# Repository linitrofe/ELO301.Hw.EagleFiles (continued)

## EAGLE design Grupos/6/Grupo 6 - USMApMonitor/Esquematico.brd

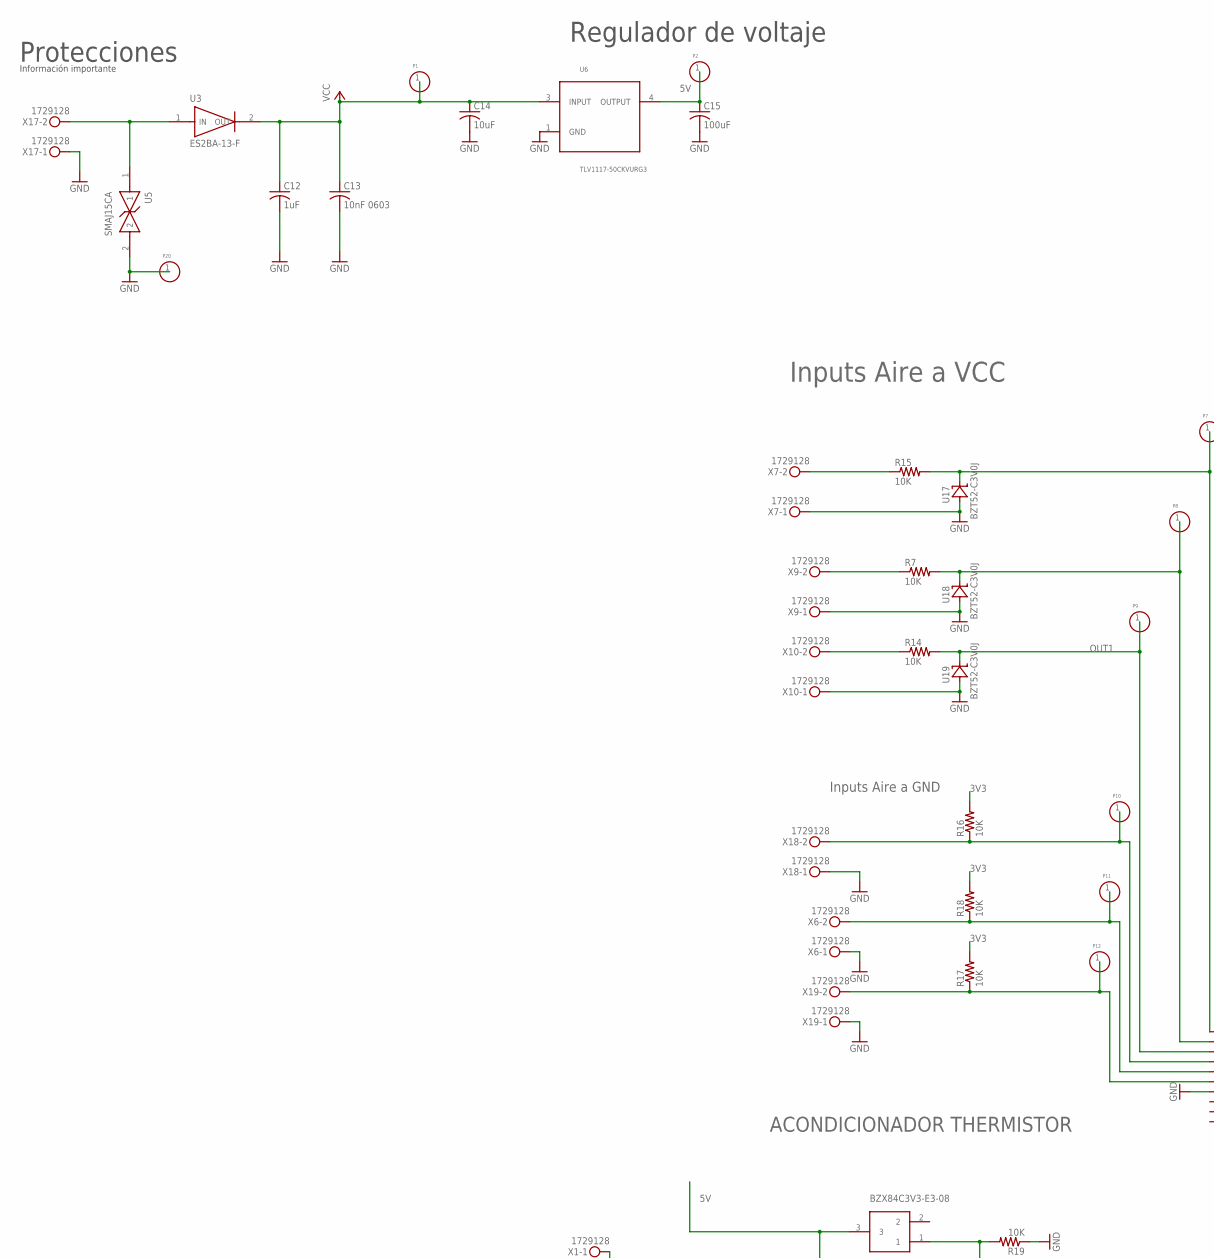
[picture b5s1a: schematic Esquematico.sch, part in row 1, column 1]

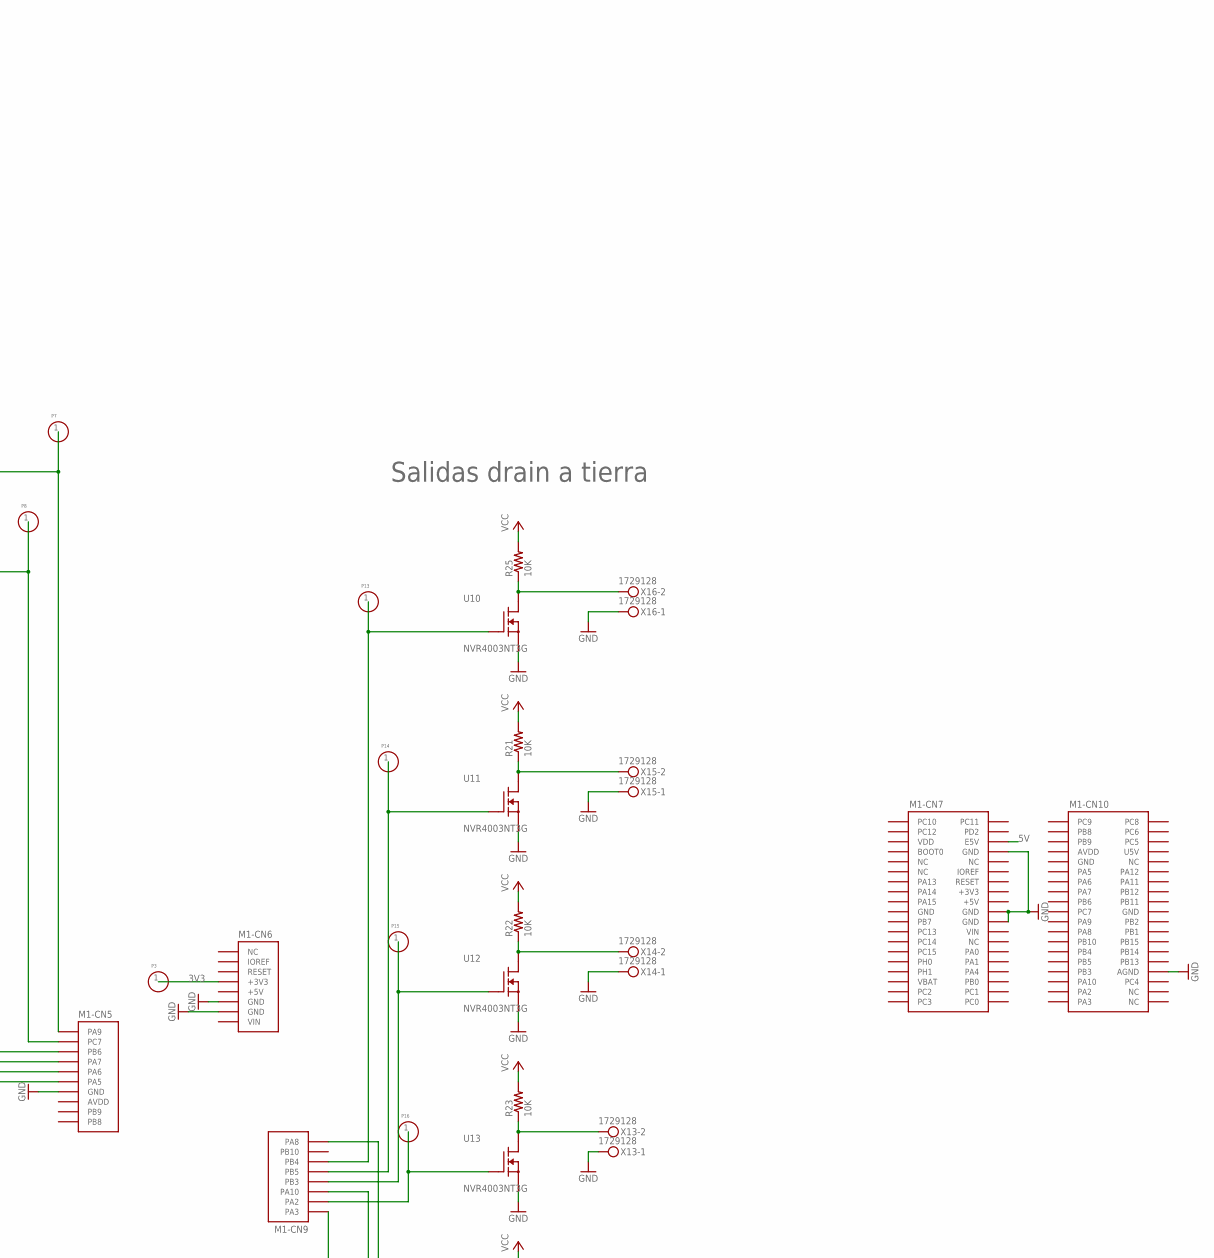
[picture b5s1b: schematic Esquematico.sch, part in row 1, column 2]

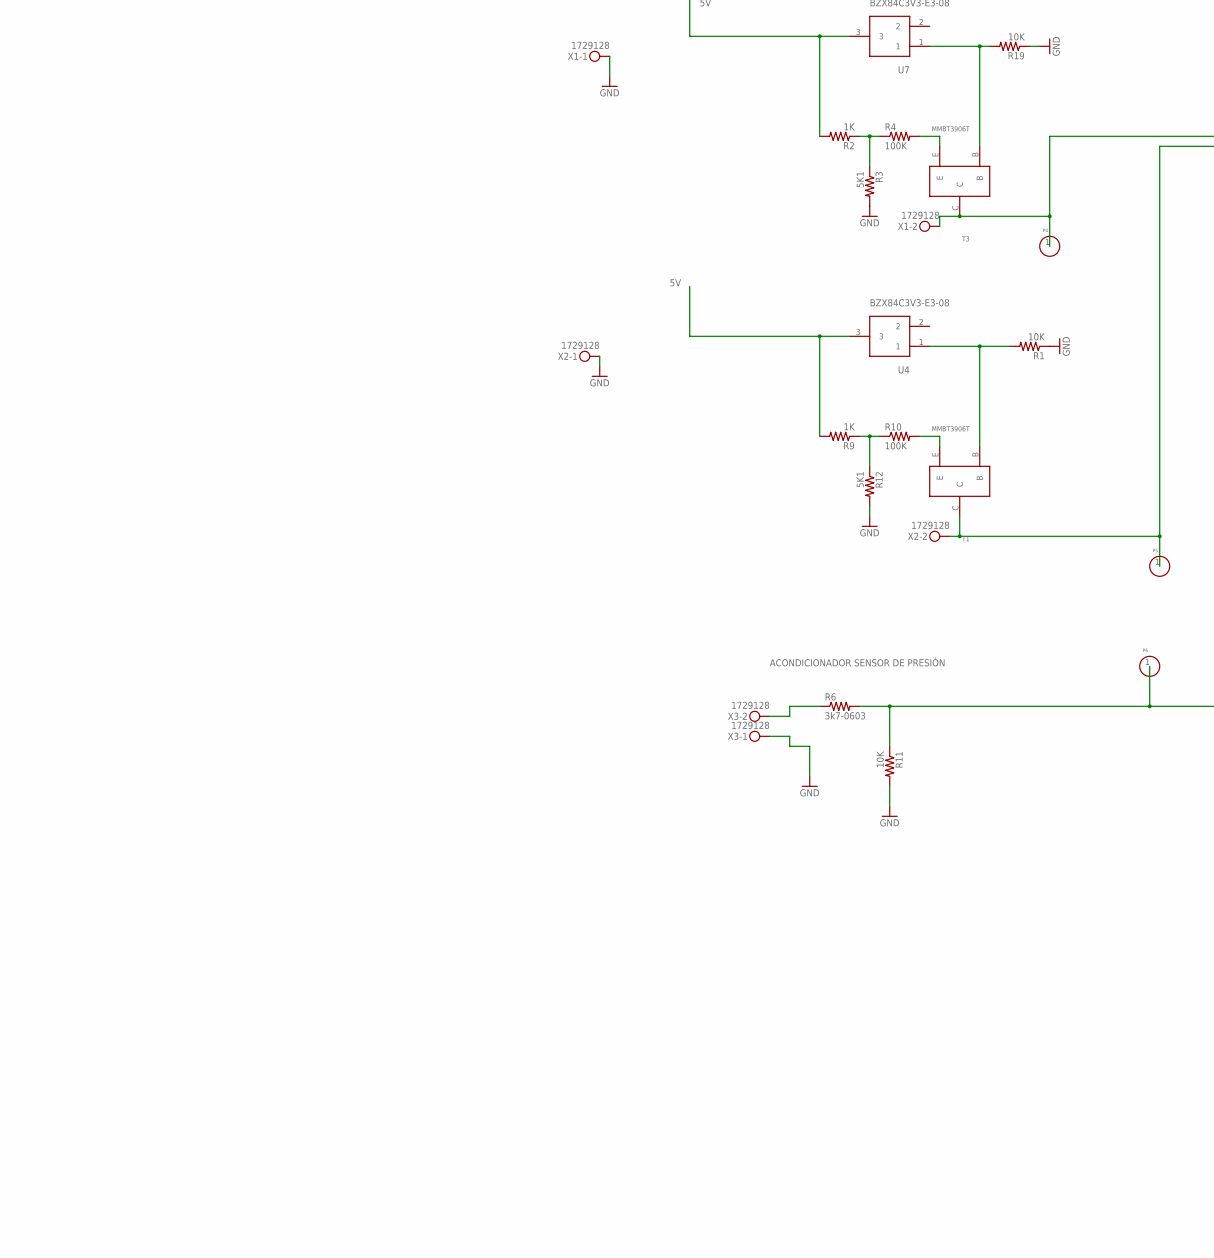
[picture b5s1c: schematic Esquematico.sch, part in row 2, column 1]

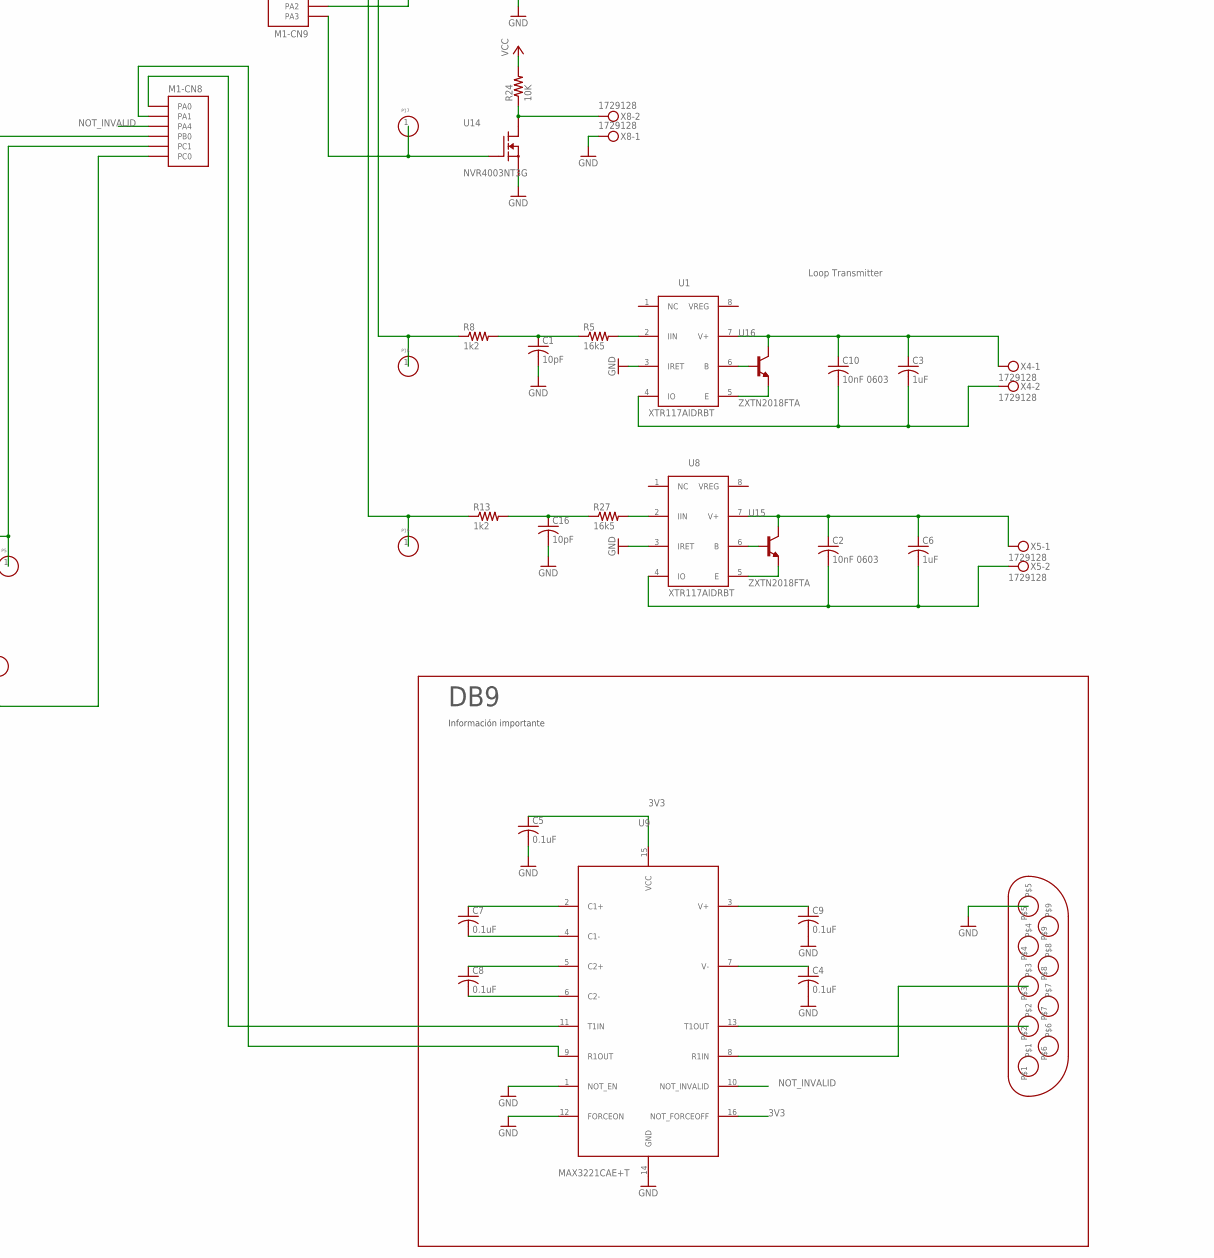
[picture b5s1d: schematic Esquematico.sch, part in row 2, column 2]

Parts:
C1, C16: 10pF; C0805; PARTNO 0805D100J101KHT
C2, C10, C13: 10nF 0603; C0603; PARTNO GCM188R72A103KA37D
C3, C6, C12: 1uF; C0805; PARTNO GCM21BR71E105KA56L
C4, C5, C7, C8, C9: 0.1uF; C0805; PARTNO GCM21BR72A104KA37L
C14: 10uF; C0805; PARTNO TCTPL1C106M8R
C15: 100uF; C0805; PARTNO TLJP107M006R5400
M1: NUCLEO-L452RE; NUCLEO-64; PARTNO NUCLEO-L452RE
P1, P2, P3, P4, P5, P6, P7, P8, P9, P10, P11, P12, P13, P14, P15, P16, P17, P18, P19, P20: TESTPOINT
R1, R7, R11, R14, R15, R16, R17, R18, R19, R21, R22, R23, R24, R25: 10K; R0805; PARTNO RK73G2ATTD1002F
R2, R9: 1K; R0805; PARTNO AC0805FR-101KL
R3, R12: 5K1; R0805; PARTNO ESR10EZPJ512
R4, R10: 100K; R0805; PARTNO AT0805FRE07100KL
R5, R27: 16k5; R0805; PARTNO ERJ-PB6B1652V
R6: 3k7-0603; R0603; PARTNO RN73H1JTTD3701B25
R8, R13: 1k2; R0805; PARTNO ESR10EZPF1R20
T1, T3: MMBT3906T; SOT-523; PARTNO MMBT3906T
U1, U8: XTR117AIDRBT; 8-SON; PARTNO XTR117AIDRBT
U2: D09P33E4GX00LF; JEDEC; PARTNO D09P33E4GX00LF
U3: ES2BA-13-F; SMA; PARTNO ES2BA-13-F
U4, U7: BZX84C3V3-E3-08; SOT-23-3; PARTNO BZX84C3V3-E3-08
U5: SMAJ15CA; DO-214AC(SMA); PARTNO SMAJ15CA
U6: TLV1117-50CKVURG3; KVU(TO-252); PARTNO TLV1117-50CKVURG3
U9: MAX3221CAE+T; 16-SSOP; PARTNO MAX3221CAE+T
U10, U11, U12, U13, U14: NVR4003NT3G; SOT-23-3; PARTNO NVR4003NT3G
U15, U16: ZXTN2018FTA; SOT23-EBC; PARTNO ZXTN2018FTA
U17, U18, U19: BZT52-C3V0J; BZT52-C3V0J-NEXPERIA; PARTNO BZT52-C3V0J
X1, X2, X3, X4, X5, X6, X7, X8, X9, X10, X13, X14, X15, X16, X17, X18, X19: 1729128; MKDSN1,5/2-5,08; PARTNO 1729128

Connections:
3V3: C5.1, M1.CN6-4 (+3V3), P3.1, R16.2, R17.2, R18.2, U9.15 (VCC), U9.16 (NOT_FORCEOFF)
5V: C15.1, M1.CN7-6 (E5V), P2.1, R2.2, R9.2, U4.3, U6.4 (OUTPUT), U7.3
+3V3: M1.CN7-16 (+3V3)
+5V: M1.CN6-5 (+5V), M1.CN7-18 (+5V)
AVDD: M1.CN5-8 (AVDD), M1.CN10-7 (AVDD)
GND: C1.2, C4.2, C5.2, C9.2, C12.2, C13.2, C14.2, C15.2, C16.2, M1.CN5-7 (GND), M1.CN6-6 (GND), M1.CN6-7 (GND), M1.CN7-8 (GND), M1.CN7-19 (GND), M1.CN7-20 (GND), M1.CN7-22 (GND), M1.CN10-9 (GND), M1.CN10-20 (GND), M1.CN10-32 (AGND), P20.1, R1.1, R3.2, R11.2, R12.2, R19.1, U1.3 (IRET), U2.P$5, U5.2, U6.1 (GND), U8.3 (IRET), U9.1 (NOT_EN), U9.12 (FORCEON), U9.14 (GND), U10.2 (SOURCE), U11.2 (SOURCE), U12.2 (SOURCE), U13.2 (SOURCE), U14.2 (SOURCE), U17.1 (ANODE), U18.1 (ANODE), U19.1 (ANODE), X1.1, X2.1, X3.1, X6.1, X7.1, X8.1, X9.1, X10.1, X13.1, X14.1, X15.1, X16.1, X17.1, X18.1, X19.1
IOREF: M1.CN6-2 (IOREF)
unnamed: R19.2, T3.B, U7.1
unnamed: R2.1, R3.1, R4.1
unnamed: R4.2, T3.E
unnamed: M1.CN9-8 (PA8), P18.1, R8.1
unnamed: M1.CN8-6 (PC0), P6.1, R6.2, R11.1
unnamed: R6.1, X3.2
unnamed: C1.1, R5.1, R8.2
unnamed: R5.2, U1.2 (IIN)
unnamed: C16.1, R13.2, R27.1
unnamed: C3.2, C10.2, U1.4 (IO), X4.2
unnamed: U1.6 (B), U16.B
unnamed: U1.5 (E), U16.E
unnamed: R1.2, T1.B, U4.1
unnamed: R9.1, R10.1, R12.1
unnamed: R10.2, T1.E
unnamed: M1.CN8-5 (PC1), P5.1, T1.C, X2.2
unnamed: C3.1, C10.1, U1.7 (V+), U16.C, X4.1
unnamed: R27.2, U8.2 (IIN)
unnamed: C2.2, C6.2, U8.4 (IO), X5.2
unnamed: U8.6 (B), U15.B
unnamed: U8.5 (E), U15.E
unnamed: C2.1, C6.1, U8.7 (V+), U15.C, X5.1
unnamed: R15.1, X7.2
unnamed: M1.CN5-1 (PA9), P7.1, R15.2, U17.2 (CATODE)
unnamed: M1.CN5-4 (PA7), P10.1, R16.1, X18.2
unnamed: R7.1, X9.2
unnamed: M1.CN5-2 (PC7), P8.1, R7.2, U18.2 (CATODE)
unnamed: R14.1, X10.2
unnamed: M1.CN5-5 (PA6), P11.1, R18.1, X6.2
unnamed: M1.CN5-6 (PA5), P12.1, R17.1, X19.2
unnamed: R21.1, U11.3 (DRAIN), X15.2
unnamed: M1.CN9-5 (PB5), P14.1, U11.1 (GATE)
unnamed: R22.1, U12.3 (DRAIN), X14.2
unnamed: M1.CN9-4 (PB3), P15.1, U12.1 (GATE)
unnamed: R23.1, U13.3 (DRAIN), X13.2
unnamed: M1.CN9-2 (PA2), P16.1, U13.1 (GATE)
unnamed: R24.1, U14.3 (DRAIN), X8.2
unnamed: M1.CN9-1 (PA3), P17.1, U14.1 (GATE)
unnamed: R25.1, U10.3 (DRAIN), X16.2
unnamed: M1.CN9-6 (PB4), P13.1, U10.1 (GATE)
unnamed: M1.CN9-3 (PA10), P19.1, R13.1
unnamed: M1.CN8-4 (PB0), P4.1, T3.C, X1.2
unnamed: C4.1, U9.7 (V-)
unnamed: C9.1, U9.3 (V+)
unnamed: C7.1, U9.2 (C1+)
unnamed: C7.2, U9.4 (C1-)
unnamed: C8.1, U9.5 (C2+)
unnamed: C8.2, U9.6 (C2-)
unnamed: U2.P$2, U9.13 (T1OUT)
unnamed: U2.P$3, U9.8 (R1IN)
unnamed: U3.1 (IN), U5.1, X17.2
unnamed: M1.CN8-1 (PA0), U9.11 (T1IN)
unnamed: M1.CN8-2 (PA1), U9.9 (R1OUT)
NOT_INVALID: M1.CN8-3 (PA4), U9.10 (NOT_INVALID)
OUT1: M1.CN5-3 (PB6), P9.1, R14.2, U19.2 (CATODE)
U5V: M1.CN10-8 (U5V)
VBAT: M1.CN7-33 (VBAT)
VCC: C12.1, C13.1, C14.1, P1.1, R21.2, R22.2, R23.2, R24.2, R25.2, U3.2 (OUT), U6.3 (INPUT)
VDD: M1.CN7-5 (VDD)
VIN: M1.CN6-8 (VIN), M1.CN7-24 (VIN)

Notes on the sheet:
ACONDICIONADOR THERMISTOR
ACONDICIONADOR SENSOR DE PRESIÓN
Salidas drain a tierra
Inputs Aire a VCC
Inputs Aire a GND
Loop Transmitter
DB9
Información importante
Protecciones
Regulador de voltaje

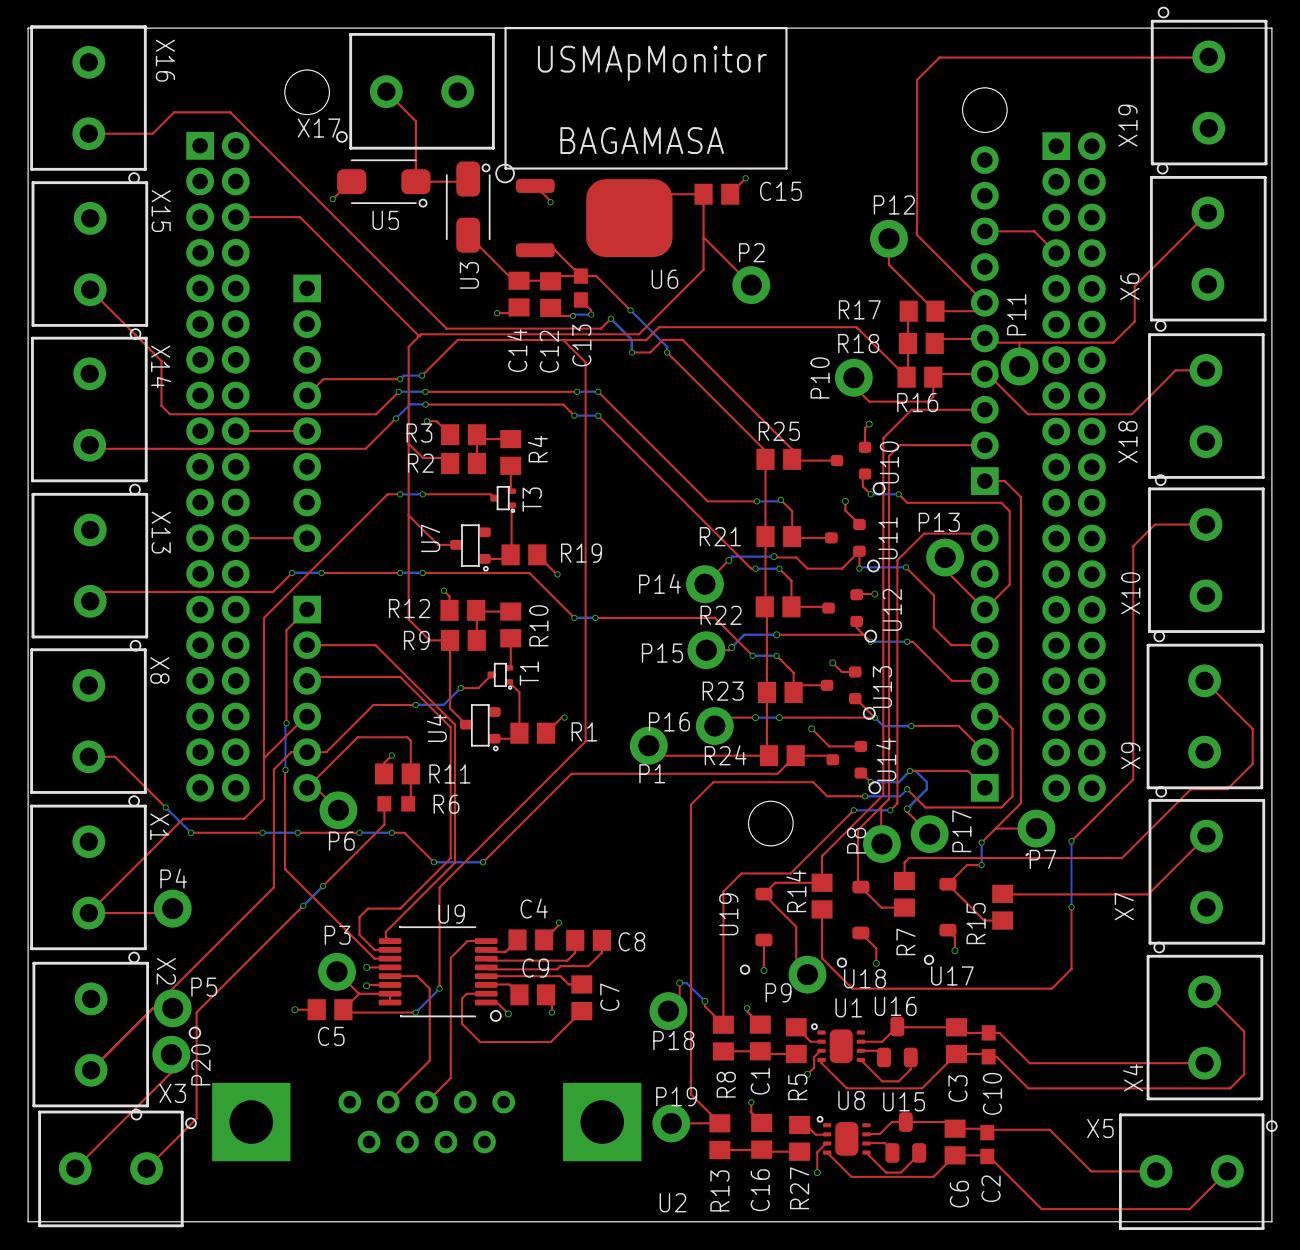
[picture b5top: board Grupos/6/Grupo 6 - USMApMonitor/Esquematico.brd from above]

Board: 2 copper layers, 88.6 x 85.0 mm, 99 parts (0 on the bottom side), 62 nets.

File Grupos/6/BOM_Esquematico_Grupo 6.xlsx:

Qty | Value | Device | Package | Parts | Description | PARTNO | POPULARITY | SPICEPREFIX | Column1
3 | BZT52-C3V0J | BZT52-C3V0J-NEXPERIA | BZT52-C3V0J-NEXPERIA | U17, U18, U19 |  | BZT52-C3V0J
2 | BZX84C3V3-E3-08 | BZX84C3V3-E3-08_VISHAY | SOT-23-3 | U4, U7 |  | BZX84C3V3-E3-08
3 | 10nF 0603 | C-USC0603 | C0603 | C2, C10, C13 | CAPACITOR, American symbol | GCM188R72A103KA37D | 37 | C
2 | 10pF | C-USC0805 | C0805 | C1, C16 | CAPACITOR, American symbol | 0805D100J101KHT | 63 | C
3 | 1uF | C-USC0805 | C0805 | C3, C6, C12 | CAPACITOR, American symbol | GCM21BR71E105KA56L | 63 | C
5 | 0.1uF | C-USC0805 | C0805 | C4, C5, C7, C8, C9 | CAPACITOR, American symbol | GCM21BR72A104KA37L | 63 | C
1 | 10uF | C-USC0805 | C0805 | C14 | CAPACITOR, American symbol | TCTPL1C106M8R | 63 | C
1 | 100uF | C-USC0805 | C0805 | C15 | CAPACITOR, American symbol | TLJP107M006R5400 | 63 | C
1 | D09P33E4GX00LF | D09P33E4GX00LF | JEDEC | U2 |  | D09P33E4GX00LF
1 | ES2BA-13-F | ES2BA-13-F | SMA | U3 |  | ES2BA-13-F
1 | MAX3221CAE+T | MAX3221CAE+T-AD | 16-SSOP | U9 |  | MAX3221CAE+T
17 | 1729128 | MKDSN1,5/2-5,08 | MKDSN1,5/2-5,08 | X1, X2, X3, X4, X5, X6, X7, X8, X9, X10, X13, X14, X15, X16, X17, X18, X19 | MKDSN 1,5/ 2-5,08 Printklemme | 1729128 | 14
2 | MMBT3906T | MMBT3906T | SOT-523 | T1, T3 |  | MMBT3906T
1 | NUCLEO-L452RE | NUCLEO-L452RE | NUCLEO-64 | M1 | No existe un outline (Layer Dimension) para esta librería. En su lugar se utili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 | NUCLEO-L452RE
5 | NVR4003NT3G | NVR4003NT3-ONSEMI | SOT-23-3 | U10, U11, U12, U13, U14 |  | NVR4003NT3G
1 | 3k7-0603 | R-US_R0603 | R0603 | R6 | RESISTOR, American symbol | RN73H1JTTD3701B25 | 77 | R
2 | 1K | R-US_R0805 | R0805 | R2, R9 | RESISTOR, American symbol | AC0805FR-101KL | 85 | R
2 | 100K | R-US_R0805 | R0805 | R4, R10 | RESISTOR, American symbol | AT0805FRE07100KL | 85 | R
2 | 16k5 | R-US_R0805 | R0805 | R5, R27 | RESISTOR, American symbol | ERJ-PB6B1652V | 85 | R
2 | 1k2 | R-US_R0805 | R0805 | R8, R13 | RESISTOR, American symbol | ESR10EZPF1R20 | 85 | R
2 | 5K1 | R-US_R0805 | R0805 | R3, R12 | RESISTOR, American symbol | ESR10EZPJ512 | 85 | R
14 | 10K | R-US_R0805 | R0805 | R1, R7, R11, R14, R15, R16, R17, R18, R19, R21, R22, R23, R24, R25 | RESISTOR, American symbol | RK73G2ATTD1002F | 85 | R
1 | SMAJ15CA | SMAJ15CA | DO-214AC(SMA) | U5 |  | SMAJ15CA
20 |  | TESTPOINT | TESTPOINT | P1, P2, P3, P4, P5, P6, P7, P8, P9, P10, P11, P12, P13, P14, P15, P16, P17, P18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
1 | TLV1117-50CKVURG3 | TLV1117-50CKVURG3 | KVU(TO-252) | U6 |  | TLV1117-50CKVURG3
2 | XTR117AIDRBT | XTR117AIDRBT-TI | 8-SON | U1, U8 |  | XTR117AIDRBT
2 | ZXTN2018FTA | ZXTN2018FTA | SOT23-EBC | U15, U16 |  | ZXTN2018FTA

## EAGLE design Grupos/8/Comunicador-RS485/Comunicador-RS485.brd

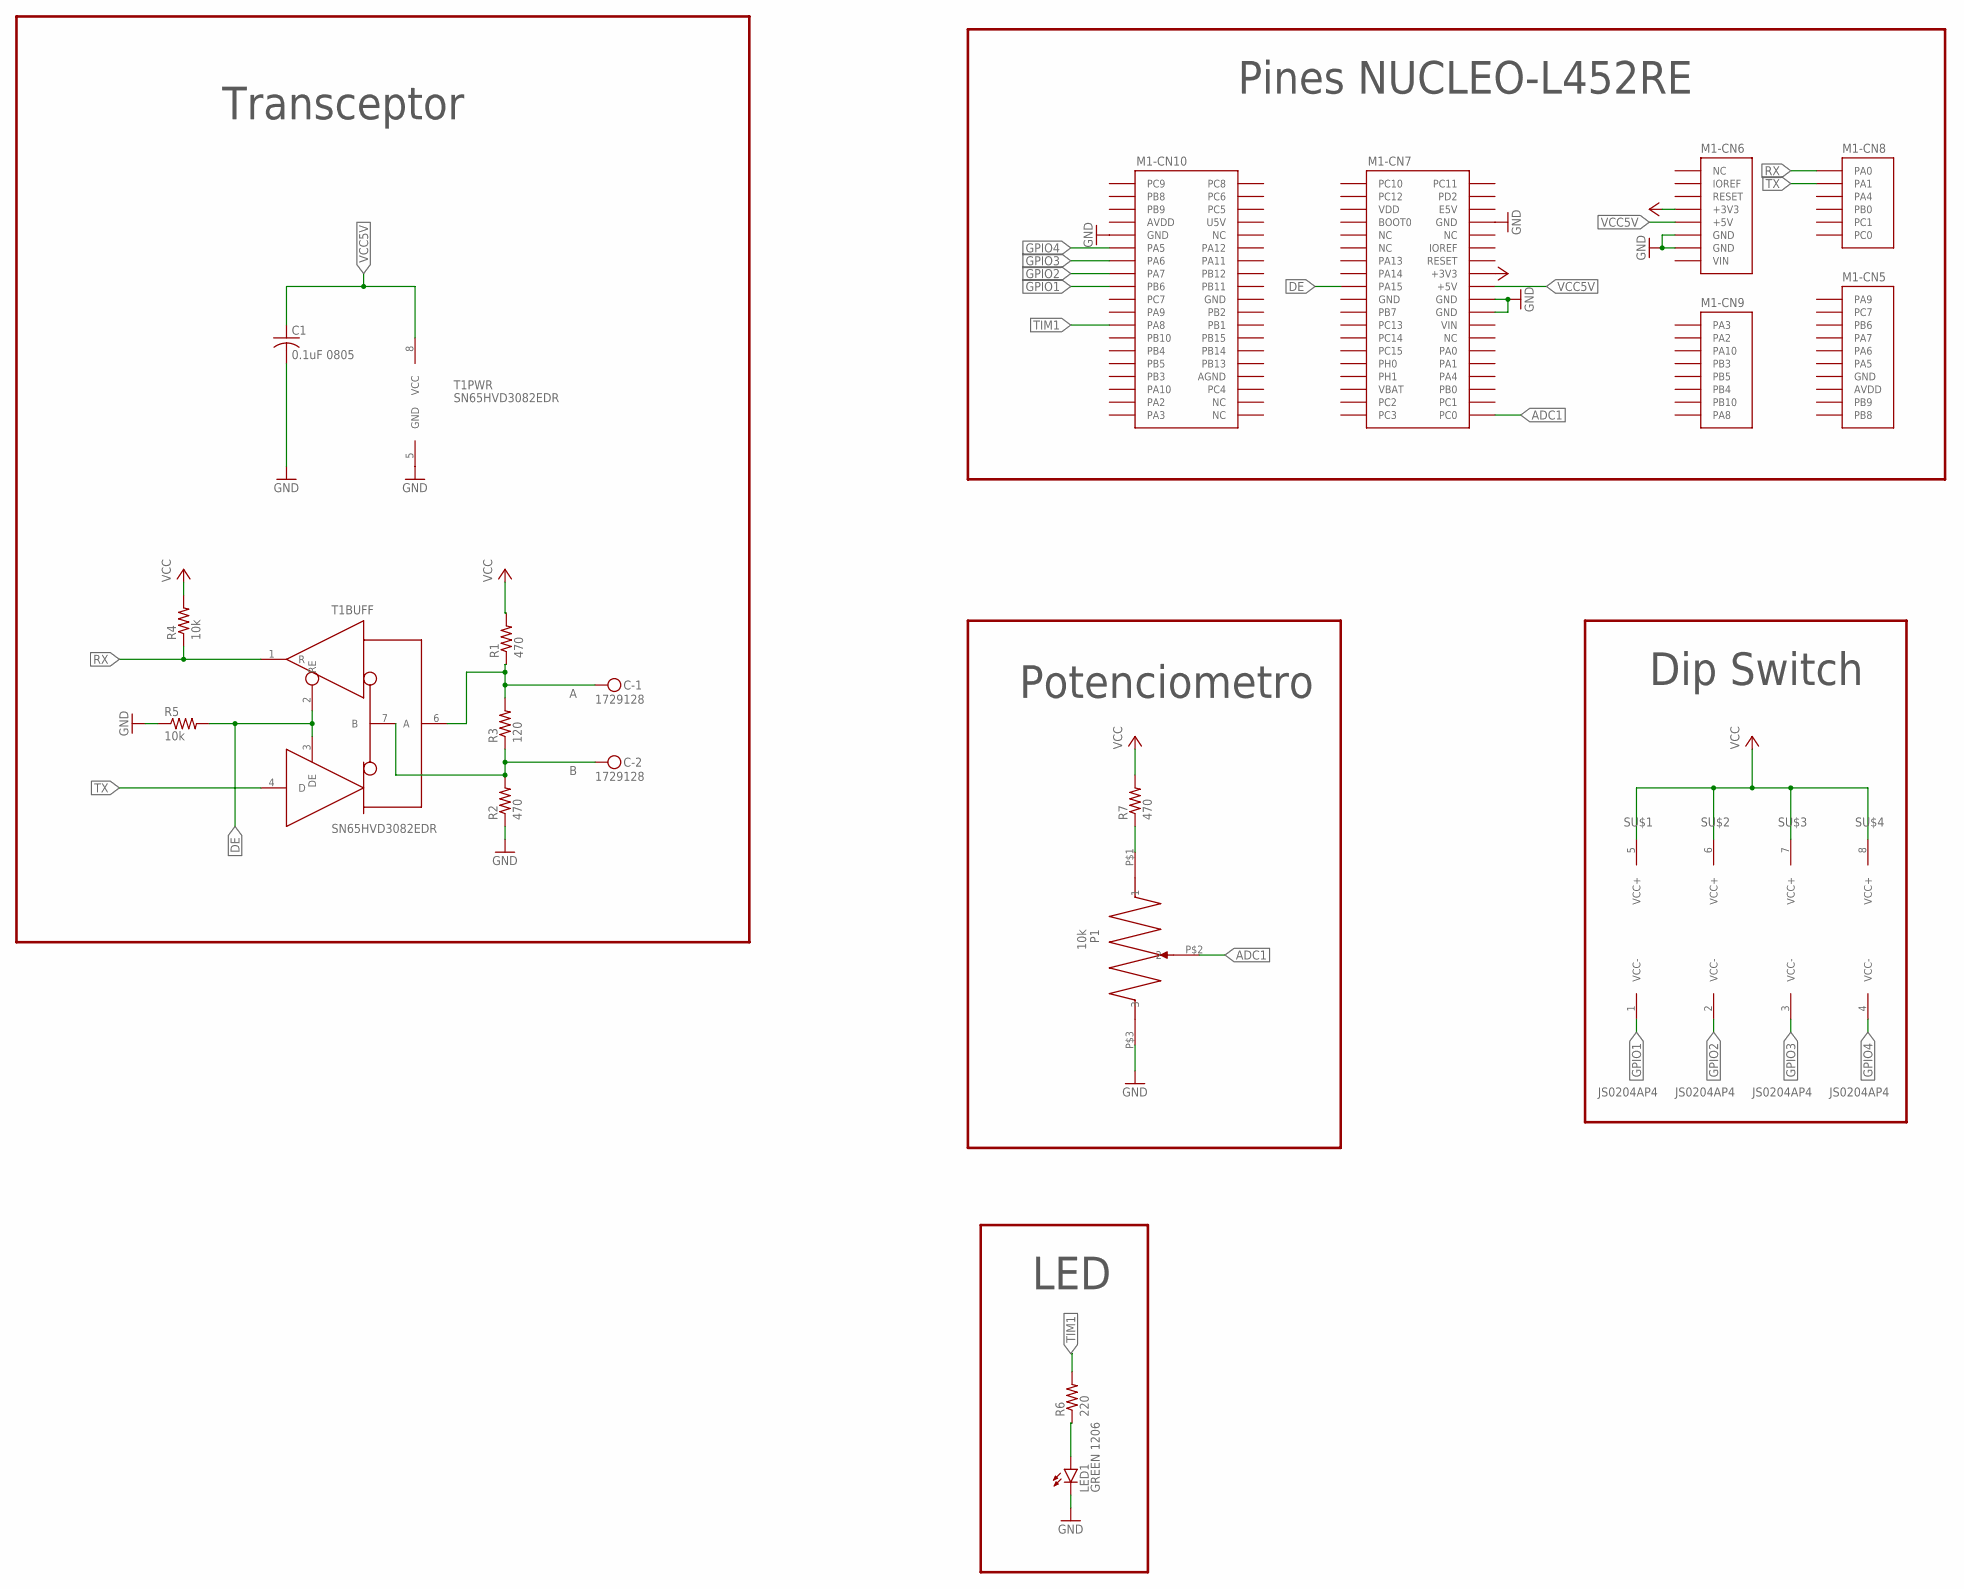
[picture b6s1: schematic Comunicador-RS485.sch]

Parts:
C: 1729128; MKDSN1,5/2-5,08; PARTNO 1729128
C1: 0.1uF 0805; C0805; PARTNO 08053C104KAT2A
LED1: GREEN 1206; CHIPLED_1206; PARTNO CMD15-21VGD/TR8
M1: NUCLEO-L452RE; NUCLEO-64; PARTNO NUCLEO-L452RE
P1: 10k; PTV09A-4; PARTNO PTV09A-4015U-B103
R1, R2, R7: 470; R0805; PARTNO AC0805FR-07470RL
R3: 120; R0805; PARTNO RC0805JR-13120RL
R4, R5: 10k; R0805; PARTNO RC0805FR-0710KP
R6: 220; R0805; PARTNO AC0805FR-07220RL
S: JS0204AP4; JS0204AP; PARTNO JS0204AP4
T1: SN65HVD3082EDR; 8-SOIC; PARTNO SN65HVD3082EDR

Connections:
A: C.1, R1.1, R3.2, T1.6 (A)
ADC1: M1.CN7-38 (PC0), P1.P$2 (2)
AGND: M1.CN10-32 (AGND)
AVDD: M1.CN5-8 (AVDD), M1.CN10-7 (AVDD)
B: C.2, R2.2, R3.1, T1.7 (B)
DE: M1.CN7-17 (PA15), R5.2, T1.2 (RE), T1.3 (DE)
GND: C1.2, LED1.C, M1.CN5-7 (GND), M1.CN6-6 (GND), M1.CN6-7 (GND), M1.CN7-8 (GND), M1.CN7-19 (GND), M1.CN7-20 (GND), M1.CN7-22 (GND), M1.CN10-9 (GND), M1.CN10-20 (GND), P1.P$3 (3), R2.1, R5.1, T1.5 (GND)
GPIO1: M1.CN10-17 (PB6), S.1 (VCC-)
GPIO2: M1.CN10-15 (PA7), S.2 (VCC-)
GPIO3: M1.CN10-13 (PA6), S.3 (VCC-)
GPIO4: M1.CN10-11 (PA5), S.4 (VCC-)
IOREF: M1.CN6-2 (IOREF)
unnamed: LED1.A, R6.1
unnamed: P1.P$1 (1), R7.1
RX: M1.CN8-1 (PA0), R4.1, T1.1 (R)
TIM1: M1.CN10-23 (PA8), R6.2
TX: M1.CN8-2 (PA1), T1.4 (D)
U5V: M1.CN10-8 (U5V)
VBAT: M1.CN7-33 (VBAT)
VCC: M1.CN6-4 (+3V3), M1.CN7-16 (+3V3), R1.2, R4.2, R7.2, S.5 (VCC+), S.6 (VCC+), S.7 (VCC+), S.8 (VCC+)
VCC5V: C1.1, M1.CN6-5 (+5V), M1.CN7-18 (+5V), T1.8 (VCC)
VDD: M1.CN7-5 (VDD)
VIN: M1.CN6-8 (VIN), M1.CN7-24 (VIN)

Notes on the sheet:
Pines NUCLEO-L452RE
Transceptor
Dip Switch
Potenciometro
LED

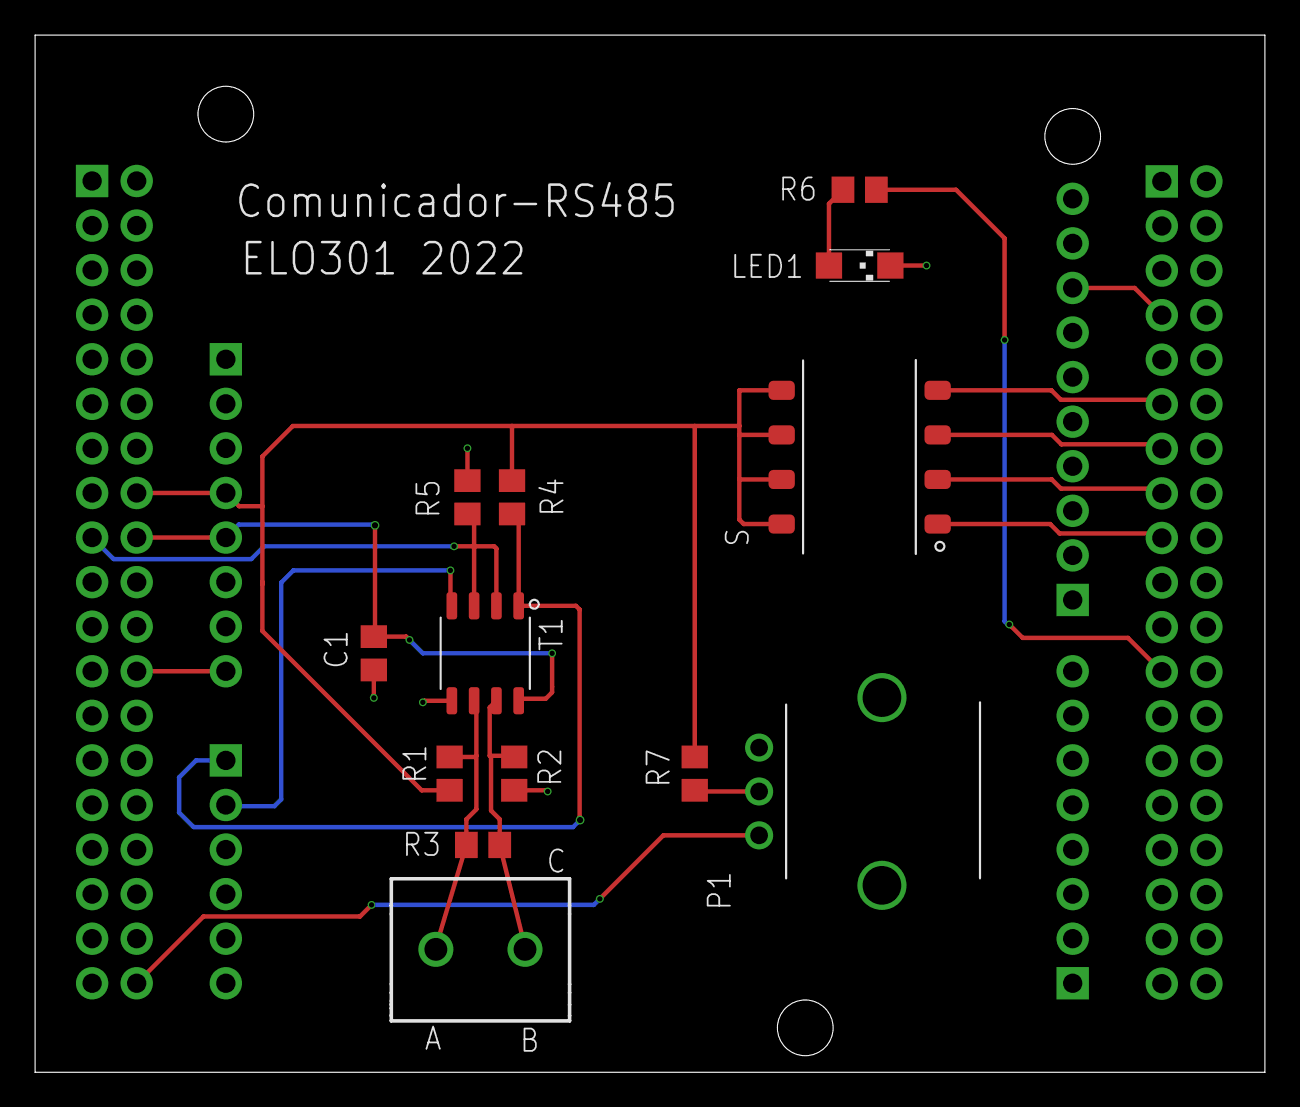
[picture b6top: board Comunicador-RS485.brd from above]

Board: 2 copper layers, 70.1 x 59.1 mm, 14 parts (0 on the bottom side), 18 nets.
